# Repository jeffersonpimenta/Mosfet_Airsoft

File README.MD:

# Gatilho eletrônico para AEGs

Uma opção às encontradas no mercado brasileiro, custo inferior sem perca de qualidade!

## Modos de funcionamento

1. Modo espelhamento: Não faz nenhuma programação no modo de disparo.
2. Modo rajada: Cada toque dispara n tiros configurados
3. Modo econômico: Cada rajada dispara apenas n tiros configurados

## Como configurar

1. Segure o gatilho e conecte a bateria
2. Ao ouvir o primeiro bipe, aperte o gatilho de acordo com o modo desejado (1, 2 ou 3).
3. Segure o gatilho até ouvir um bipe contínuo para confirmar.
4. Se o modo configurado for o 2 ou o 3, precisamos configurar a quantidade de disparos! Ponha a arma no semi-automático e dê dois disparos. Um bipe será ouvido quando a operação for concluída.
5. Aperte o gatilho de acordo com a quantidade de disparos configuradas.
6. Segure até ouvir um bipe contínuo.
7. Feito!

A demonstração pode ser vista [aqui](https://www.youtube.com/watch?v=d0rjX8GWv6M&t=5s)

## Quais as vantagens em relação ao gatilho stock da AEG?

- [x] Evita o desgaste prematuro dos contatos mecânicos
- [x] Leve ganho de cadência
- [x] Uma leve economia de bateria
- [x] Controle total dos disparos

## Arquivos e fotos

* /BRD - Esquemático e desenho da placa
A placa pode ser comprada [aqui](https://www.curtacircuitos.com.br/jeffersonpimenta/Gatilho) 
* /CODE - [Código fonte](https://github.com/jeffersonpimenta/Mosfet_Airsoft/tree/master/Code)
* /Imagens - [Fotos](https://github.com/jeffersonpimenta/Mosfet_Airsoft/tree/master/Imagens)

A placa pode ser encomendada pelo link https://www.curtacircuitos.com.br/jeffersonpimenta/Gatilho 

Custa apenas 8,82 reais a unidade e abaixo uma imagem das placas produzidas.

# Observações
* O microcontrolador que deve ser utilizado tem referência Attiny85, não o Attiny13 como mostrado no esquemático, apenas uma falta da biblioteca para o dispositivo. Ambos são da mesma família e possuem a mesma pinagem
* Utilizar Atmel Studio 7.0

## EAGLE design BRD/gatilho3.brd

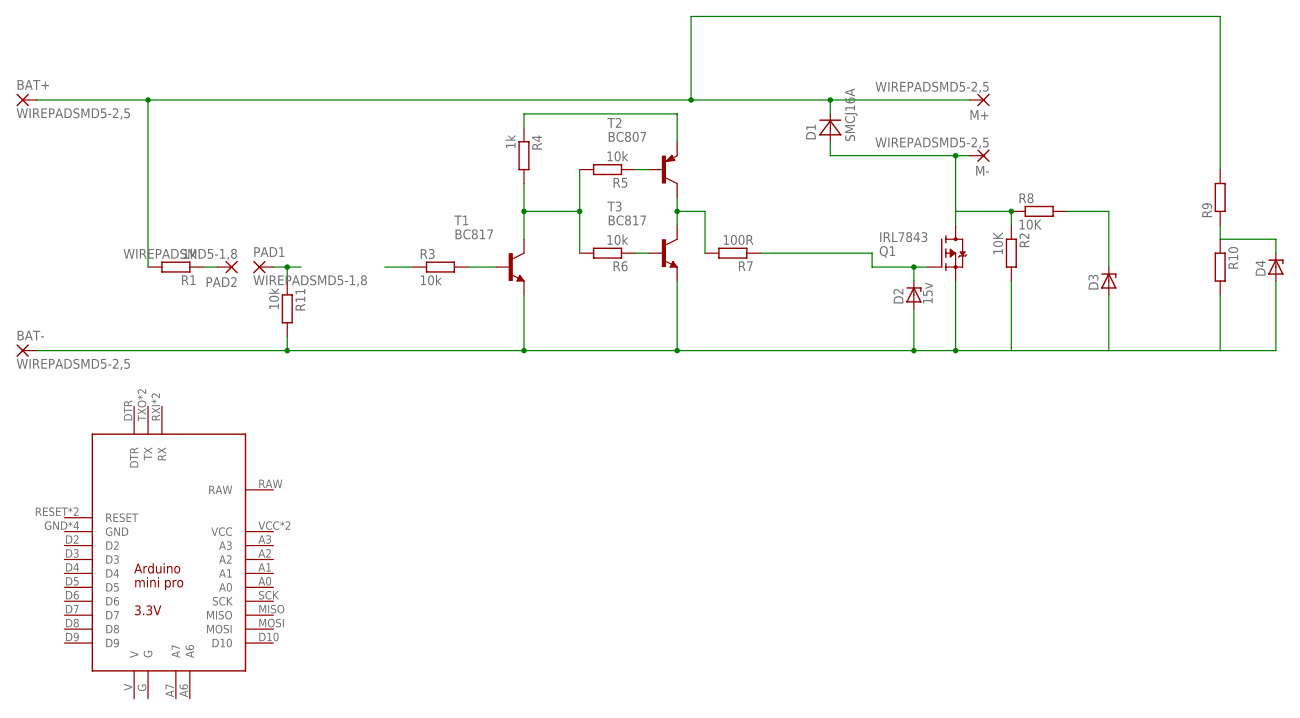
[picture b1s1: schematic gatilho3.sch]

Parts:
BAT+: WIREPADSMD5-2,5; 5-2,5
BAT-: WIREPADSMD5-2,5; 5-2,5
D1: SMCJ16A; SMA
D2: 15v; SOD80C
D3, D4: ZENER-DIODESOD80C; SOD80C
M+: WIREPADSMD5-2,5; 5-2,5
M-: WIREPADSMD5-2,5; 5-2,5
PAD1, PAD2: WIREPADSMD5-1,8; 5-1,8
Q1: IRL7843; TO252
R1, R4: 1k; R0805
R2, R8: 10K; R0805
R3, R5, R6, R11: 10k; R0805
R7: 100R; R0805
R9, R10: R-EU_R0805; R0805
T1, T3: BC817; SOT23-BEC
T2: BC807; SOT23-BEC
U$1: ARDUINO_MINI_PRO_3V3

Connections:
unnamed: BAT-.1, D2.A, D3.A, D4.A, Q1.2 (S), R2.2, R10.2, R11.2, T1.E, T3.E
unnamed: D1.A, M-.1, Q1.3 (D), R2.1, R8.1
unnamed: D4.C, R9.1, R10.1
unnamed: PAD2.1, R1.1
unnamed: BAT+.1, D1.C, M+.1, R1.2, R9.2
unnamed: PAD1.1, R11.1
unnamed: D3.C, R8.2
unnamed: R4.1, T2.E
unnamed: R4.2, R5.2, R6.2, T1.C
unnamed: R3.2, T1.B
unnamed: R7.2, T2.C, T3.C
unnamed: R5.1, T2.B
unnamed: R6.1, T3.B
unnamed: D2.C, Q1.1 (G), R7.1

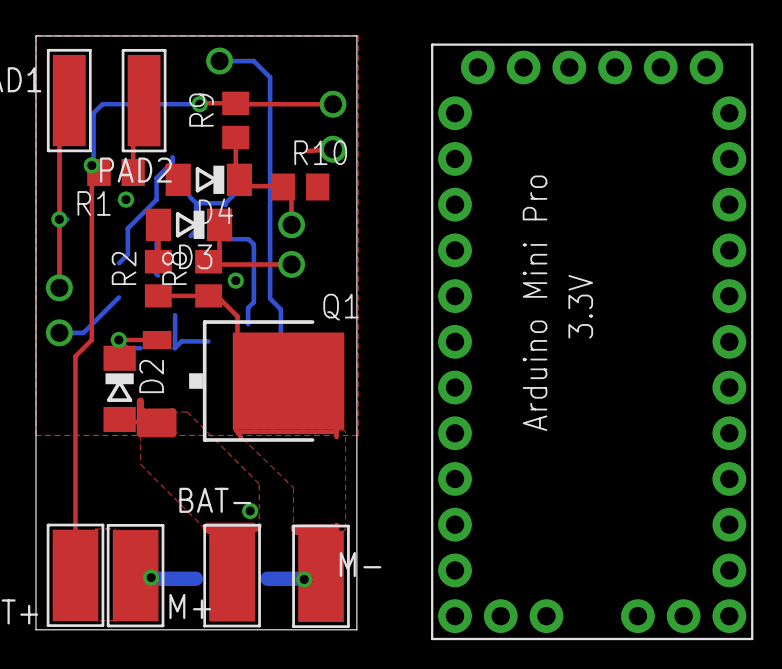
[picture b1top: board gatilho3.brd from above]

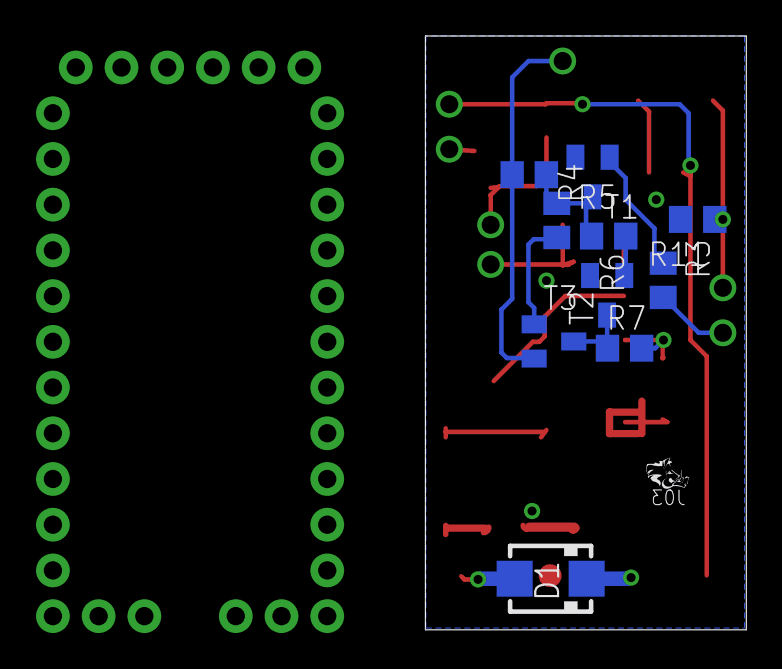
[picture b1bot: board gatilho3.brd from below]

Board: 2 copper layers, 17.8 x 33.0 mm, 26 parts (10 on the bottom side), 14 nets.

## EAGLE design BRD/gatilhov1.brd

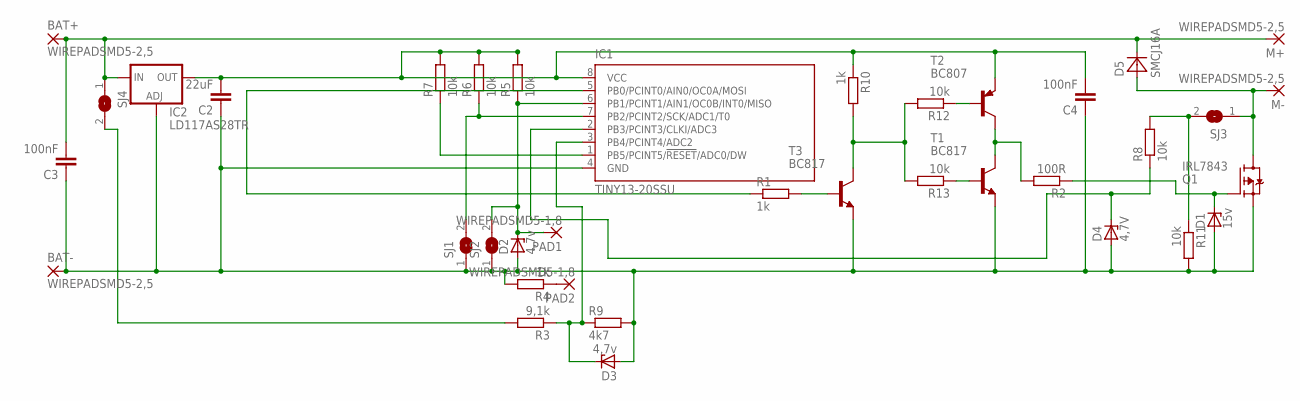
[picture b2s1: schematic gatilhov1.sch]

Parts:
BAT+: WIREPADSMD5-2,5; 5-2,5
BAT-: WIREPADSMD5-2,5; 5-2,5
C2: 22uF; C1210K
C3: 100nF; C0805K
C4: 100nF; C1206K
D1: 15v; SOD80C
D2, D3: 4,7v; SOD80C
D4: 4,7V; SOD80C
D5: SMCJ16A; SMA
IC1: TINY13-20SSU; 8S1
IC2: LD117AS28TR; SOT223
M+: WIREPADSMD5-2,5; 5-2,5
M-: WIREPADSMD5-2,5; 5-2,5
PAD1, PAD2: WIREPADSMD5-1,8; 5-1,8
Q1: IRL7843; TO252
R1, R4, R10: 1k; R0805
R2: 100R; R0805
R3: 9,1k; R0805
R5, R6, R7, R8, R11, R12, R13: 10k; R0805
R9: 4k7; R0805
SJ1, SJ2, SJ3, SJ4: SJ
T1, T3: BC817; SOT23-BEC
T2: BC807; SOT23-BEC

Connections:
unnamed 0: BAT-.1, C2.1, C3.1, C4.1, D1.A, D2.A, D3.A, D4.A, IC1.4 (GND), IC2.1 (ADJ), Q1.2 (S), R4.2, R9.2, R11.2, SJ1.1, SJ2.1, T1.E, T3.E; also elsewhere on the board
unnamed: D5.A, M-.1, Q1.3 (D), SJ3.1
unnamed: PAD2.1, R4.1
unnamed: D4.C, IC1.2 (PB3/PCINT3/CLKI/ADC3), R8.1
unnamed 4: IC1.5 (PB0/PCINT0/AIN0/OC0A/MOSI), R1.1; also elsewhere on the board
unnamed: D2.C, IC1.6 (PB1/PCINT1/AIN1/OC0B/INT0/MISO), PAD1.1, R5.1, SJ2.2
unnamed: D3.C, IC1.3 (PB4/PCINT4/ADC2), R3.1, R9.1
unnamed: IC1.7 (PB2/PCINT2/SCK/ADC1/T0), R6.1, SJ1.2
unnamed: IC1.1 (PB5/PCINT5/!RESET!/ADC0/DW), R7.1
unnamed: R10.2, R12.2, R13.2, T3.C
unnamed: R1.2, T3.B
unnamed: R2.2, T1.C, T2.C
unnamed: BAT+.1, C3.2, D5.C, IC2.3 (IN), M+.1, SJ4.1
unnamed: R12.1, T2.B
unnamed: R13.1, T1.B
unnamed: D1.C, Q1.1 (G), R2.1
unnamed: R3.2, SJ4.2
unnamed: R8.2, R11.1, SJ3.2
unnamed: C2.2, C4.2, IC1.8 (VCC), IC2.4 (OUT), R5.2, R6.2, R7.2, R10.1, T2.E

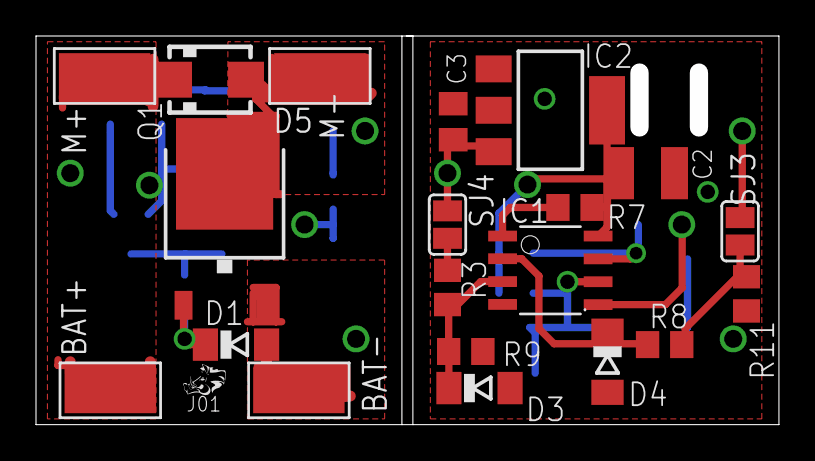
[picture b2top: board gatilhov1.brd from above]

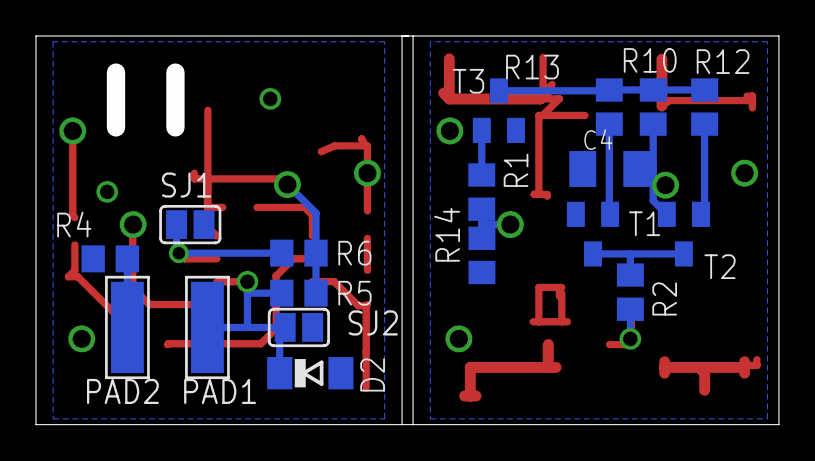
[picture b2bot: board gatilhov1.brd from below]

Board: 2 copper layers, 41.3 x 21.6 mm, 38 parts (18 on the bottom side), 19 nets.

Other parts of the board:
R14: 10k; R0805

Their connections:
unnamed 0: R14.1; also elsewhere on the board
unnamed 4: R14.2; also elsewhere on the board
